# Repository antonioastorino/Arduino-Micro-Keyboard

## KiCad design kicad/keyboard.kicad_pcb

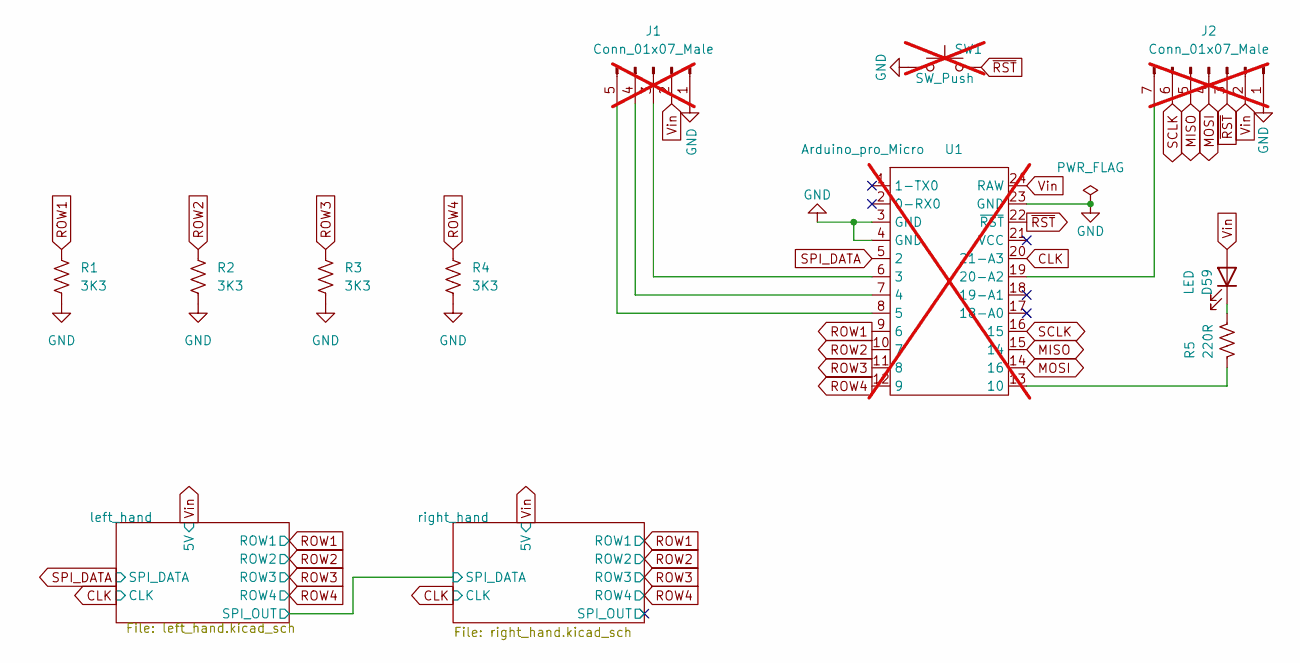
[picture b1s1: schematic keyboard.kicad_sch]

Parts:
D59: LED; LED_0805_2012Metric; LCSC C2296
J1: Conn_01x07_Male; PinHeader_1x05_P2.54mm_Vertical; not fitted
J2: Conn_01x07_Male; PinHeader_01x07; not fitted
R1, R2, R3, R4: 3K3; R_0603_1608Metric; LCSC C22978
R5: 220R; R_0603_1608Metric; LCSC C22962
SW1: SW_Push; DIP-2_P5.08mm; not fitted
U1: Arduino_pro_Micro; DIP-24_W15.24mm; not fitted

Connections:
CLK: U1.20 (21-A3); also elsewhere on the board
GND: J1.1, J2.1, R1.2, R2.2, R3.2, R4.2, SW1.1, U1.3 (GND), U1.4 (GND), U1.23 (GND); also elsewhere on the board
MISO: J2.5, U1.15 (14)
MOSI: J2.4, U1.14 (16)
unnamed: D59.1 (K), R5.2
unnamed: J1.3, U1.6 (3)
unnamed: J1.4, U1.7 (4)
unnamed: J1.5, U1.8 (5)
unnamed: J2.7, U1.19 (20-A2)
unnamed: R5.1, U1.13 (10)
ROW1: R1.1, U1.9 (6); also elsewhere on the board
ROW2: R2.1, U1.10 (7); also elsewhere on the board
ROW3: R3.1, U1.11 (8); also elsewhere on the board
ROW4: R4.1, U1.12 (9); also elsewhere on the board
SCLK: J2.6, U1.16 (15)
SPI_DATA: U1.5 (2); also elsewhere on the board
Vin: D59.2 (A), J1.2, J2.2, U1.24 (RAW); also elsewhere on the board
~RST: J2.3, SW1.2, U1.22 (~RST)

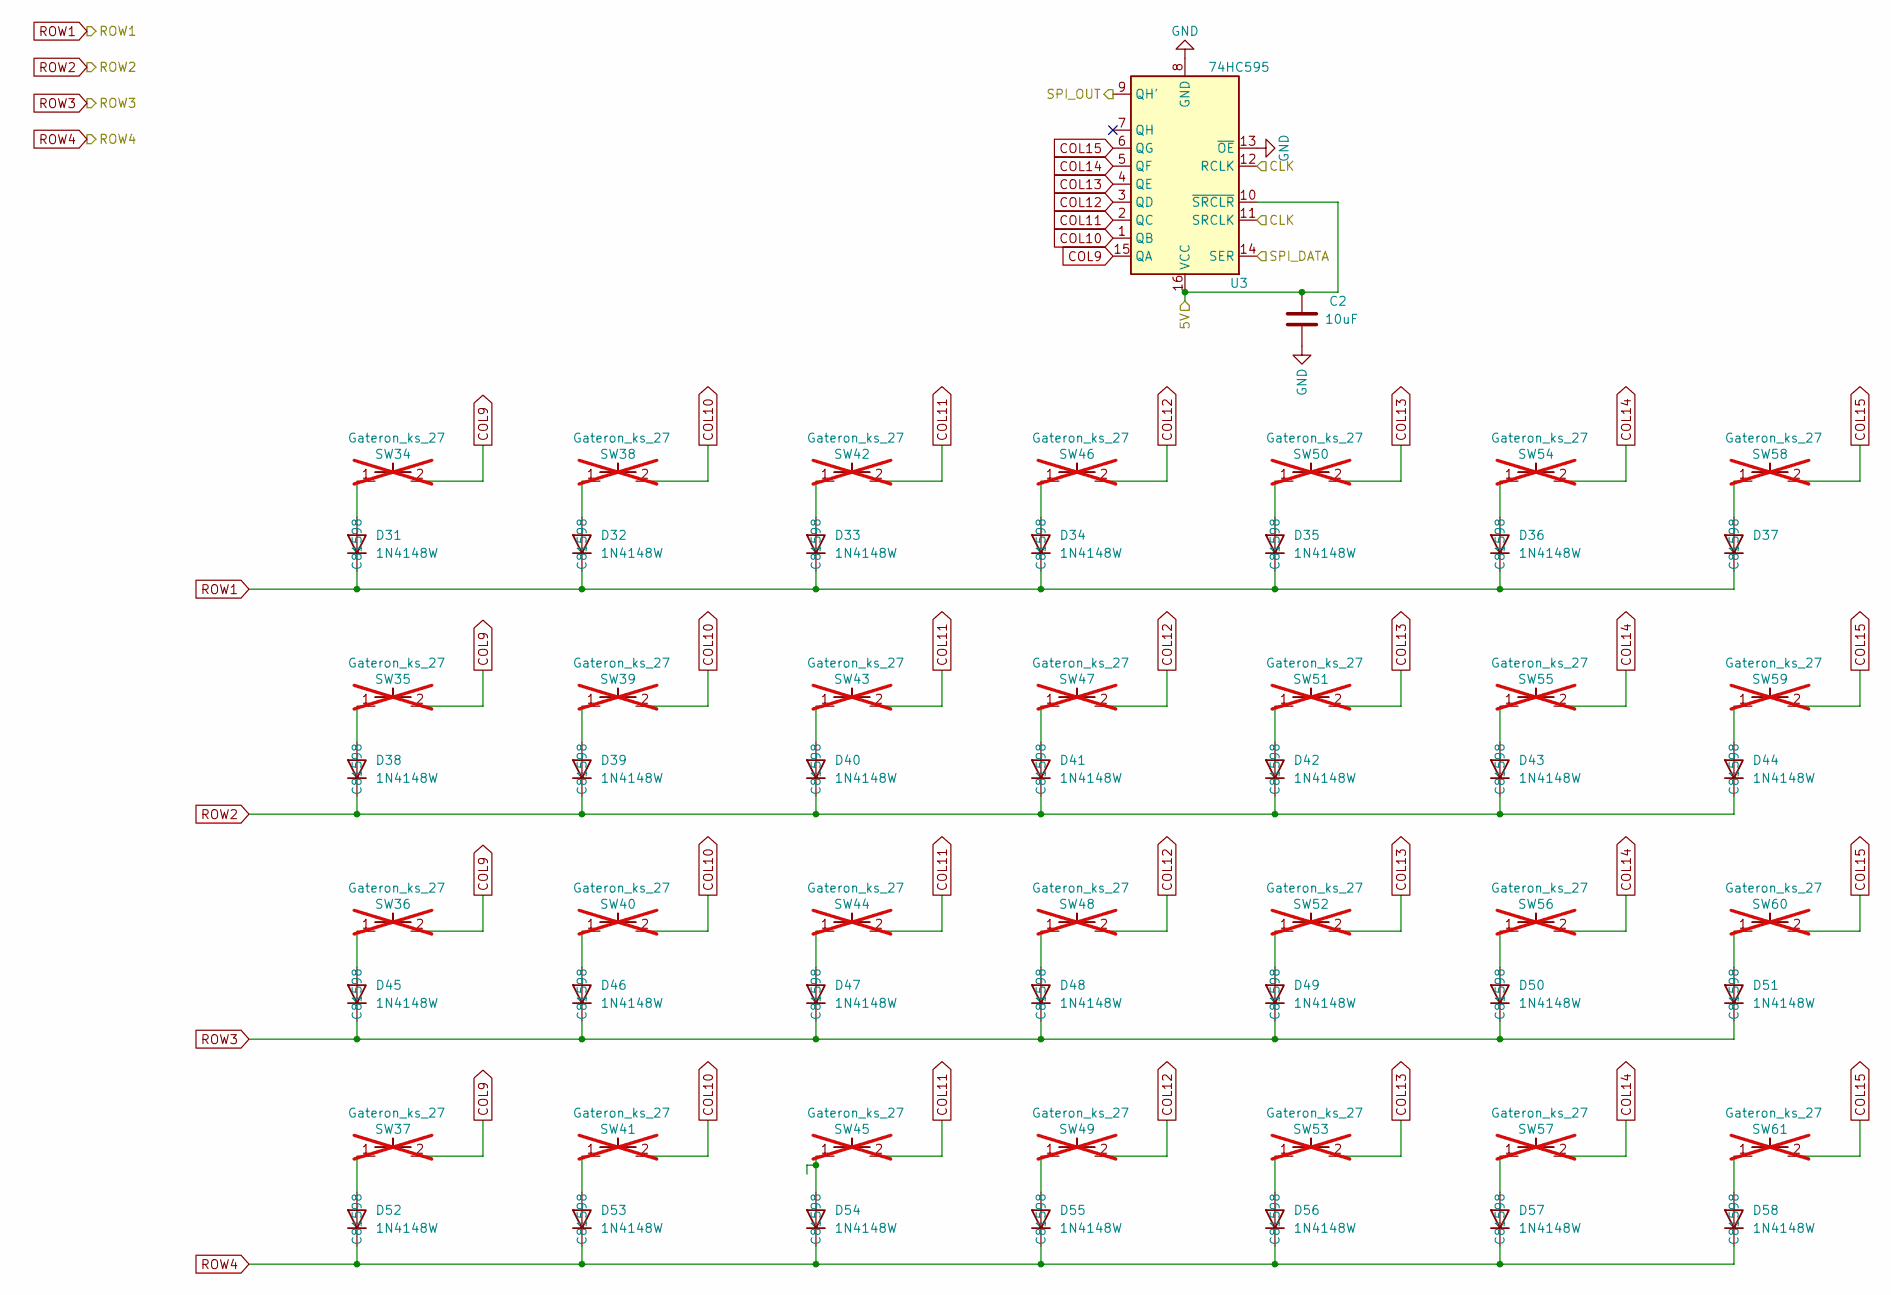
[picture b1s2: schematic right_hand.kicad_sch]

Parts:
C2: 10uF; C_0603_1608Metric; LCSC C19702
D31, D32, D33, D34, D35, D36, D37, D38, D39, D40, D41, D42, D43, D44, D45, D46, D47, D48, D49, D50, D51, D52, D53, D54, D55, D56, D57, D58: 1N4148W; D_SOD-123; LCSC C81598
SW34, SW35, SW36, SW37, SW38, SW39, SW40, SW41, SW42, SW43, SW44, SW45, SW46, SW47, SW48, SW49, SW50, SW51, SW52, SW53, SW54, SW55, SW56, SW57, SW58, SW59, SW60, SW61: Gateron_ks_27; not fitted
U3: 74HC595; SO-16_3.9x9.9mm_P1.27mm; LCSC C5947

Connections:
/left_hand/SPI_OUT: U3.14 (SER); also elsewhere on the board
/right_hand/SPI_OUT: U3.9 (QH')
CLK: U3.11 (SRCLK), U3.12 (RCLK); also elsewhere on the board
COL9: SW34.2, SW35.2, SW36.2, SW37.2, U3.15 (QA)
COL10: SW38.2, SW39.2, SW40.2, SW41.2, U3.1 (QB)
COL11: SW42.2, SW43.2, SW44.2, SW45.2, U3.2 (QC)
COL12: SW46.2, SW47.2, SW48.2, SW49.2, U3.3 (QD)
COL13: SW50.2, SW51.2, SW52.2, SW53.2, U3.4 (QE)
COL14: SW54.2, SW55.2, SW56.2, SW57.2, U3.5 (QF)
COL15: SW58.2, SW59.2, SW60.2, SW61.2, U3.6 (QG)
GND: C2.2, U3.8 (GND), U3.13 (~OE); also elsewhere on the board
unnamed: D31.2 (A), SW34.1
unnamed: D32.2 (A), SW38.1
unnamed: D33.2 (A), SW42.1
unnamed: D34.2 (A), SW46.1
unnamed: D35.2 (A), SW50.1
unnamed: D36.2 (A), SW54.1
unnamed: D37.2 (A), SW58.1
unnamed: D38.2 (A), SW35.1
unnamed: D39.2 (A), SW39.1
unnamed: D40.2 (A), SW43.1
unnamed: D41.2 (A), SW47.1
unnamed: D42.2 (A), SW51.1
unnamed: D43.2 (A), SW55.1
unnamed: D44.2 (A), SW59.1
unnamed: D45.2 (A), SW36.1
unnamed: D46.2 (A), SW40.1
unnamed: D47.2 (A), SW44.1
unnamed: D48.2 (A), SW48.1
unnamed: D49.2 (A), SW52.1
unnamed: D50.2 (A), SW56.1
unnamed: D51.2 (A), SW60.1
unnamed: D52.2 (A), SW37.1
unnamed: D53.2 (A), SW41.1
unnamed: D54.2 (A), SW45.1
unnamed: D55.2 (A), SW49.1
unnamed: D56.2 (A), SW53.1
unnamed: D57.2 (A), SW57.1
unnamed: D58.2 (A), SW61.1
ROW1: D31.1 (K), D32.1 (K), D33.1 (K), D34.1 (K), D35.1 (K), D36.1 (K), D37.1 (K); also elsewhere on the board
ROW2: D38.1 (K), D39.1 (K), D40.1 (K), D41.1 (K), D42.1 (K), D43.1 (K), D44.1 (K); also elsewhere on the board
ROW3: D45.1 (K), D46.1 (K), D47.1 (K), D48.1 (K), D49.1 (K), D50.1 (K), D51.1 (K); also elsewhere on the board
ROW4: D52.1 (K), D53.1 (K), D54.1 (K), D55.1 (K), D56.1 (K), D57.1 (K), D58.1 (K); also elsewhere on the board
Vin: C2.1, U3.10 (~SRCLR), U3.16 (VCC); also elsewhere on the board

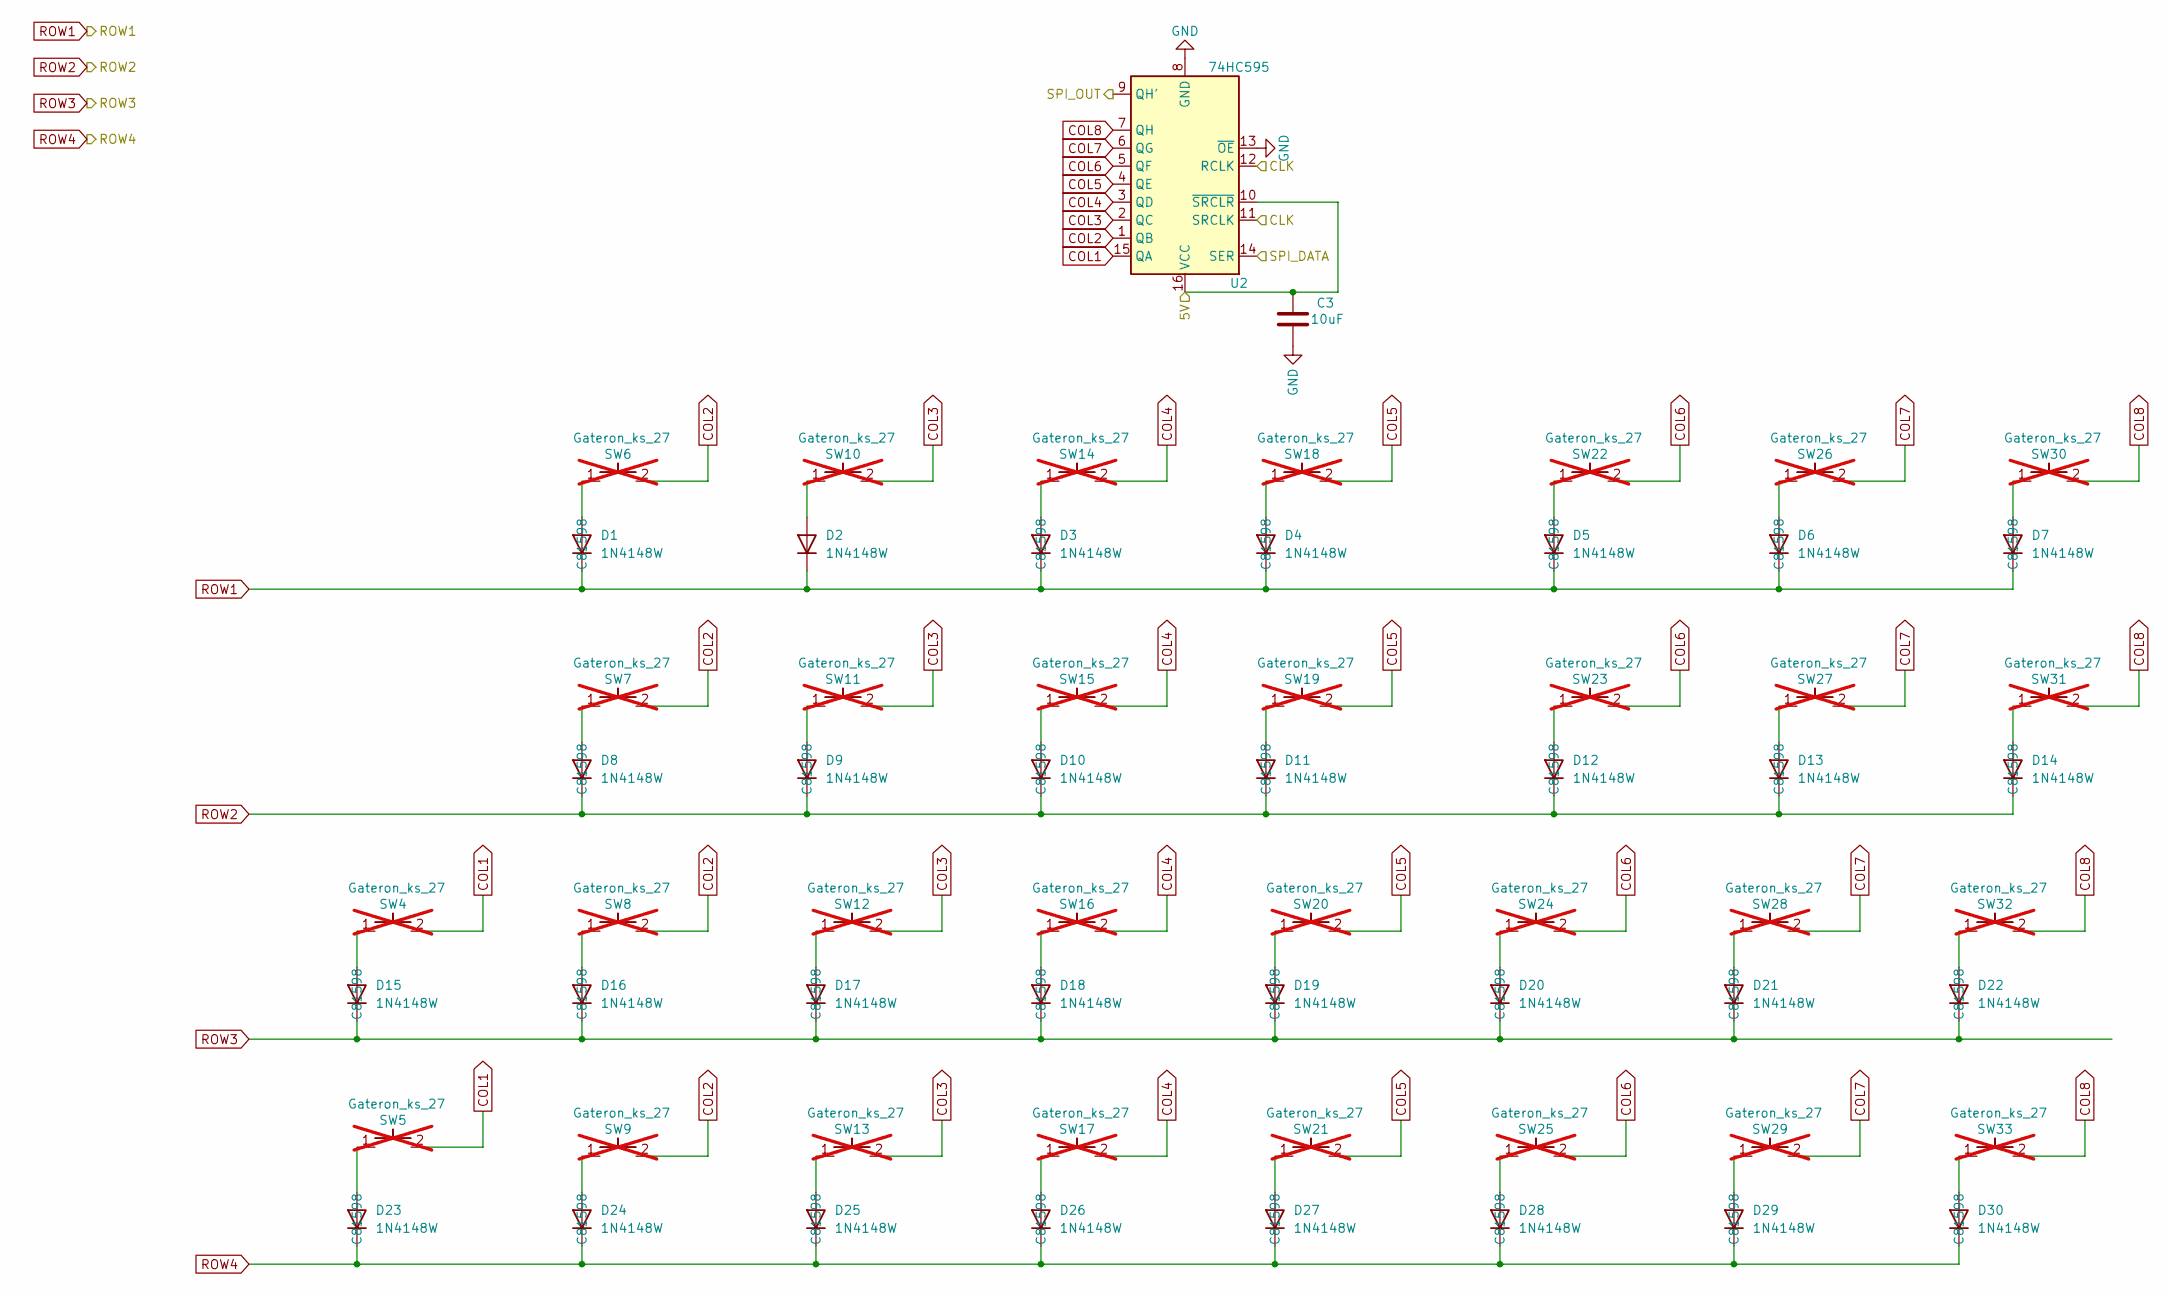
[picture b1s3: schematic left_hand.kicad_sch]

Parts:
C3: 10uF; C_0603_1608Metric; LCSC C19702
D1, D2, D3, D4, D5, D6, D7, D8, D9, D10, D11, D12, D13, D14, D15, D16, D17, D18, D19, D20, D21, D22, D23, D24, D25, D26, D27, D28, D29, D30: 1N4148W; D_SOD-123; LCSC C81598
SW4, SW5, SW6, SW7, SW8, SW9, SW10, SW11, SW12, SW13, SW14, SW15, SW16, SW17, SW18, SW19, SW20, SW21, SW22, SW23, SW24, SW25, SW26, SW27, SW28, SW29, SW30, SW31, SW32, SW33: Gateron_ks_27; not fitted
U2: 74HC595; SO-16_3.9x9.9mm_P1.27mm; LCSC C5947

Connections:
/left_hand/SPI_OUT: U2.9 (QH'); also elsewhere on the board
CLK: U2.11 (SRCLK), U2.12 (RCLK); also elsewhere on the board
COL1: SW4.2, SW5.2, U2.15 (QA)
COL2: SW6.2, SW7.2, SW8.2, SW9.2, U2.1 (QB)
COL3: SW10.2, SW11.2, SW12.2, SW13.2, U2.2 (QC)
COL4: SW14.2, SW15.2, SW16.2, SW17.2, U2.3 (QD)
COL5: SW18.2, SW19.2, SW20.2, SW21.2, U2.4 (QE)
COL6: SW22.2, SW23.2, SW24.2, SW25.2, U2.5 (QF)
COL7: SW26.2, SW27.2, SW28.2, SW29.2, U2.6 (QG)
COL8: SW30.2, SW31.2, SW32.2, SW33.2, U2.7 (QH)
GND: C3.2, U2.8 (GND), U2.13 (~OE); also elsewhere on the board
unnamed: D1.2 (A), SW6.1
unnamed: D2.2 (A), SW10.1
unnamed: D3.2 (A), SW14.1
unnamed: D4.2 (A), SW18.1
unnamed: D5.2 (A), SW22.1
unnamed: D6.2 (A), SW26.1
unnamed: D7.2 (A), SW30.1
unnamed: D8.2 (A), SW7.1
unnamed: D9.2 (A), SW11.1
unnamed: D10.2 (A), SW15.1
unnamed: D11.2 (A), SW19.1
unnamed: D12.2 (A), SW23.1
unnamed: D13.2 (A), SW27.1
unnamed: D14.2 (A), SW31.1
unnamed: D15.2 (A), SW4.1
unnamed: D16.2 (A), SW8.1
unnamed: D17.2 (A), SW12.1
unnamed: D18.2 (A), SW16.1
unnamed: D19.2 (A), SW20.1
unnamed: D20.2 (A), SW24.1
unnamed: D21.2 (A), SW28.1
unnamed: D22.2 (A), SW32.1
unnamed: D23.2 (A), SW5.1
unnamed: D24.2 (A), SW9.1
unnamed: D25.2 (A), SW13.1
unnamed: D26.2 (A), SW17.1
unnamed: D27.2 (A), SW21.1
unnamed: D28.2 (A), SW25.1
unnamed: D29.2 (A), SW29.1
unnamed: D30.2 (A), SW33.1
ROW1: D1.1 (K), D2.1 (K), D3.1 (K), D4.1 (K), D5.1 (K), D6.1 (K), D7.1 (K); also elsewhere on the board
ROW2: D8.1 (K), D9.1 (K), D10.1 (K), D11.1 (K), D12.1 (K), D13.1 (K), D14.1 (K); also elsewhere on the board
ROW3: D15.1 (K), D16.1 (K), D17.1 (K), D18.1 (K), D19.1 (K), D20.1 (K), D21.1 (K), D22.1 (K); also elsewhere on the board
ROW4: D23.1 (K), D24.1 (K), D25.1 (K), D26.1 (K), D27.1 (K), D28.1 (K), D29.1 (K), D30.1 (K); also elsewhere on the board
SPI_DATA: U2.14 (SER); also elsewhere on the board
Vin: C3.1, U2.10 (~SRCLR), U2.16 (VCC); also elsewhere on the board

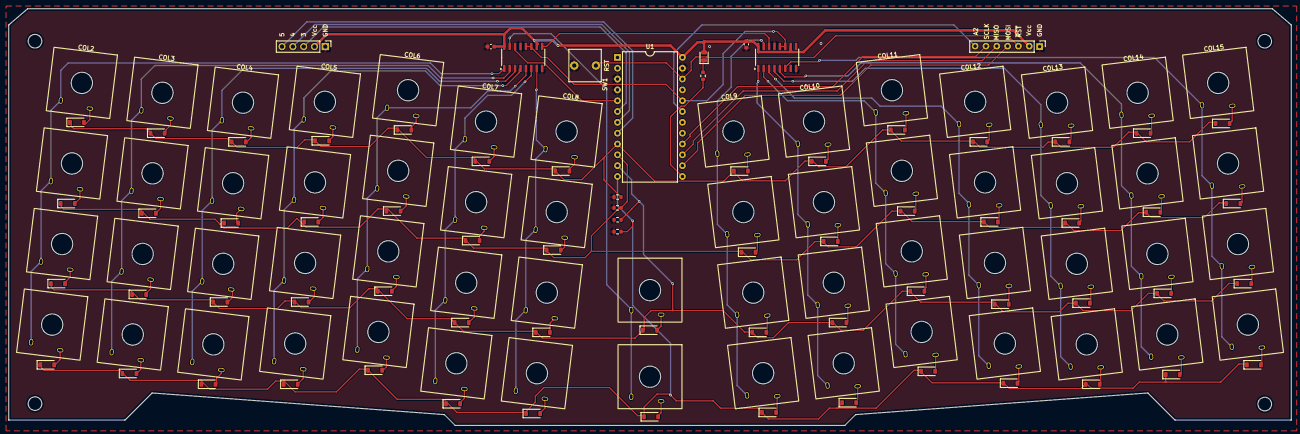
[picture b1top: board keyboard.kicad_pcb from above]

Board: 2 copper layers, 301.0 x 97.8 mm, 130 parts (0 on the bottom side), 92 nets.

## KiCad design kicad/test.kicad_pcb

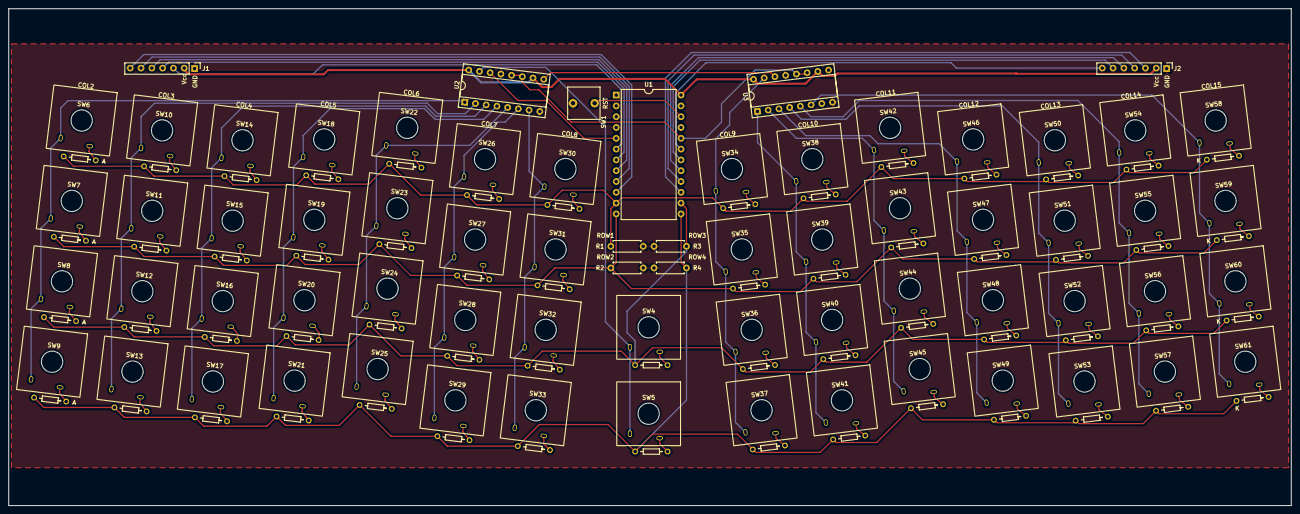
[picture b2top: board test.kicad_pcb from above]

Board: 2 copper layers, 301.6 x 116.8 mm, 68 parts (0 on the bottom side), 93 nets.

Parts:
J1, J2: Conn_01x07_Male; PinHeader_01x07
R1, R2, R3, R4: 3K3; R_Axial_DIN0207_L6.3mm_D2.5mm_P7.62mm_Horizontal
SW1: SW_Push; DIP-2_P5.08mm
SW4, SW5, SW6, SW7, SW8, SW9, SW10, SW11, SW12, SW13, SW14, SW15, SW16, SW17, SW18, SW19, SW20, SW21, SW22, SW23, SW24, SW25, SW26, SW27, SW28, SW29, SW30, SW31, SW32, SW33, SW34, SW35, SW36, SW37, SW38, SW39, SW40, SW41, SW42, SW43, SW44, SW45, SW46, SW47, SW48, SW49, SW50, SW51, SW52, SW53, SW54, SW55, SW56, SW57, SW58, SW59, SW60, SW61: Gateron_ks_27
U1: Arduino_pro_Micro; DIP-24_W15.24mm
U2, U3: 74HC595; DIP-16_W7.62mm_Socket

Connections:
/left_hand/SPI_OUT: U2.9 (QH'), U3.14 (SER)
CLK: U1.20 (21-A3), U2.11 (SRCLK), U2.12 (RCLK), U3.11 (SRCLK), U3.12 (RCLK)
COL1: SW4.2, SW5.2, U2.15 (QA)
COL2: SW6.2, SW7.2, SW8.2, SW9.2, U2.1 (QB)
COL3: SW10.2, SW11.2, SW12.2, SW13.2, U2.2 (QC)
COL4: SW14.2, SW15.2, SW16.2, SW17.2, U2.3 (QD)
COL5: SW18.2, SW19.2, SW20.2, SW21.2, U2.4 (QE)
COL6: SW22.2, SW23.2, SW24.2, SW25.2, U2.5 (QF)
COL7: SW26.2, SW27.2, SW28.2, SW29.2, U2.6 (QG)
COL8: SW30.2, SW31.2, SW32.2, SW33.2, U2.7 (QH)
COL9: SW34.2, SW35.2, SW36.2, SW37.2, U3.15 (QA)
COL10: SW38.2, SW39.2, SW40.2, SW41.2, U3.1 (QB)
COL11: SW42.2, SW43.2, SW44.2, SW45.2, U3.2 (QC)
COL12: SW46.2, SW47.2, SW48.2, SW49.2, U3.3 (QD)
COL13: SW50.2, SW51.2, SW52.2, SW53.2, U3.4 (QE)
COL14: SW54.2, SW55.2, SW56.2, SW57.2, U3.5 (QF)
COL15: SW58.2, SW59.2, SW60.2, SW61.2, U3.6 (QG)
GND: J1.1, J2.1, R1.2, R2.2, R3.2, R4.2, SW1.1, U1.3 (GND), U1.4 (GND), U1.23 (GND), U2.8 (GND), U2.13 (~OE), U3.8 (GND), U3.13 (~OE)
unnamed: J1.3, U1.6 (3)
unnamed: J1.4, U1.7 (4)
unnamed: J1.5, U1.8 (5)
unnamed: J1.6, U1.9 (6)
unnamed: J1.7, U1.10 (7)
unnamed: J2.3, U1.15 (14)
unnamed: J2.4, U1.16 (15)
unnamed: J2.5, U1.17 (18-A0)
unnamed: J2.6, U1.18 (19-A1)
unnamed: J2.7, U1.19 (20-A2)
unnamed: SW4.1, SW4.4 (A)
unnamed: SW5.1, SW5.4 (A)
unnamed: SW6.1, SW6.4 (A)
unnamed: SW7.1, SW7.4 (A)
unnamed: SW8.1, SW8.4 (A)
unnamed: SW9.1, SW9.4 (A)
unnamed: SW10.1, SW10.4 (A)
unnamed: SW11.1, SW11.4 (A)
unnamed: SW12.1, SW12.4 (A)
unnamed: SW13.1, SW13.4 (A)
unnamed: SW14.1, SW14.4 (A)
unnamed: SW15.1, SW15.4 (A)
unnamed: SW16.1, SW16.4 (A)
unnamed: SW17.1, SW17.4 (A)
unnamed: SW18.1, SW18.4 (A)
unnamed: SW19.1, SW19.4 (A)
unnamed: SW20.1, SW20.4 (A)
unnamed: SW21.1, SW21.4 (A)
unnamed: SW22.1, SW22.4 (A)
unnamed: SW23.1, SW23.4 (A)
unnamed: SW24.1, SW24.4 (A)
unnamed: SW25.1, SW25.4 (A)
unnamed: SW26.1, SW26.4 (A)
unnamed: SW27.1, SW27.4 (A)
unnamed: SW28.1, SW28.4 (A)
unnamed: SW29.1, SW29.4 (A)
unnamed: SW30.1, SW30.4 (A)
unnamed: SW31.1, SW31.4 (A)
unnamed: SW32.1, SW32.4 (A)
unnamed: SW33.1, SW33.4 (A)
unnamed: SW34.1, SW34.4 (A)
unnamed: SW35.1, SW35.4 (A)
unnamed: SW36.1, SW36.4 (A)
unnamed: SW37.1, SW37.4 (A)
unnamed: SW38.1, SW38.4 (A)
unnamed: SW39.1, SW39.4 (A)
unnamed: SW40.1, SW40.4 (A)
unnamed: SW41.1, SW41.4 (A)
unnamed: SW42.1, SW42.4 (A)
unnamed: SW43.1, SW43.4 (A)
unnamed: SW44.1, SW44.4 (A)
unnamed: SW45.1, SW45.4 (A)
unnamed: SW46.1, SW46.4 (A)
unnamed: SW47.1, SW47.4 (A)
unnamed: SW48.1, SW48.4 (A)
unnamed: SW49.1, SW49.4 (A)
unnamed: SW50.1, SW50.4 (A)
unnamed: SW51.1, SW51.4 (A)
unnamed: SW52.1, SW52.4 (A)
unnamed: SW53.1, SW53.4 (A)
unnamed: SW54.1, SW54.4 (A)
unnamed: SW55.1, SW55.4 (A)
unnamed: SW56.1, SW56.4 (A)
unnamed: SW57.1, SW57.4 (A)
unnamed: SW58.1, SW58.4 (A)
unnamed: SW59.1, SW59.4 (A)
unnamed: SW60.1, SW60.4 (A)
unnamed: SW61.1, SW61.4 (A)
ROW1: R1.1, SW6.3 (K), SW10.3 (K), SW14.3 (K), SW18.3 (K), SW22.3 (K), SW26.3 (K), SW30.3 (K), SW34.3 (K), SW38.3 (K), SW42.3 (K), SW46.3 (K), SW50.3 (K), SW54.3 (K), SW58.3 (K), U1.11 (8)
ROW2: R2.1, SW7.3 (K), SW11.3 (K), SW15.3 (K), SW19.3 (K), SW23.3 (K), SW27.3 (K), SW31.3 (K), SW35.3 (K), SW39.3 (K), SW43.3 (K), SW47.3 (K), SW51.3 (K), SW55.3 (K), SW59.3 (K), U1.12 (9)
ROW3: R3.1, SW4.3 (K), SW8.3 (K), SW12.3 (K), SW16.3 (K), SW20.3 (K), SW24.3 (K), SW28.3 (K), SW32.3 (K), SW36.3 (K), SW40.3 (K), SW44.3 (K), SW48.3 (K), SW52.3 (K), SW56.3 (K), SW60.3 (K), U1.14 (16)
ROW4: R4.1, SW5.3 (K), SW9.3 (K), SW13.3 (K), SW17.3 (K), SW21.3 (K), SW25.3 (K), SW29.3 (K), SW33.3 (K), SW37.3 (K), SW41.3 (K), SW45.3 (K), SW49.3 (K), SW53.3 (K), SW57.3 (K), SW61.3 (K), U1.13 (10)
SPI_DATA: U1.5 (2), U2.14 (SER)
Vin: J1.2, J2.2, U1.24 (RAW), U2.10 (~SRCLR), U2.16 (VCC), U3.10 (~SRCLR), U3.16 (VCC)
~RST: SW1.2, U1.22 (~RST)

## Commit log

2024-07-29 TMP: remove unused stuff
2024-07-29 Last update
2024-07-29 Update switch diode
2024-11-17 Update PCB
2024-11-29 SIPO is SMT
2024-12-11 Fix pinout
2024-12-13 Format text
2024-12-13 Add modifiers in all other layers
2024-12-13 Add modifiers to secondary layouts
2024-12-15 Use numpad instead of numbers
2025-11-29 TMP: don't send reports if no key is pressed
